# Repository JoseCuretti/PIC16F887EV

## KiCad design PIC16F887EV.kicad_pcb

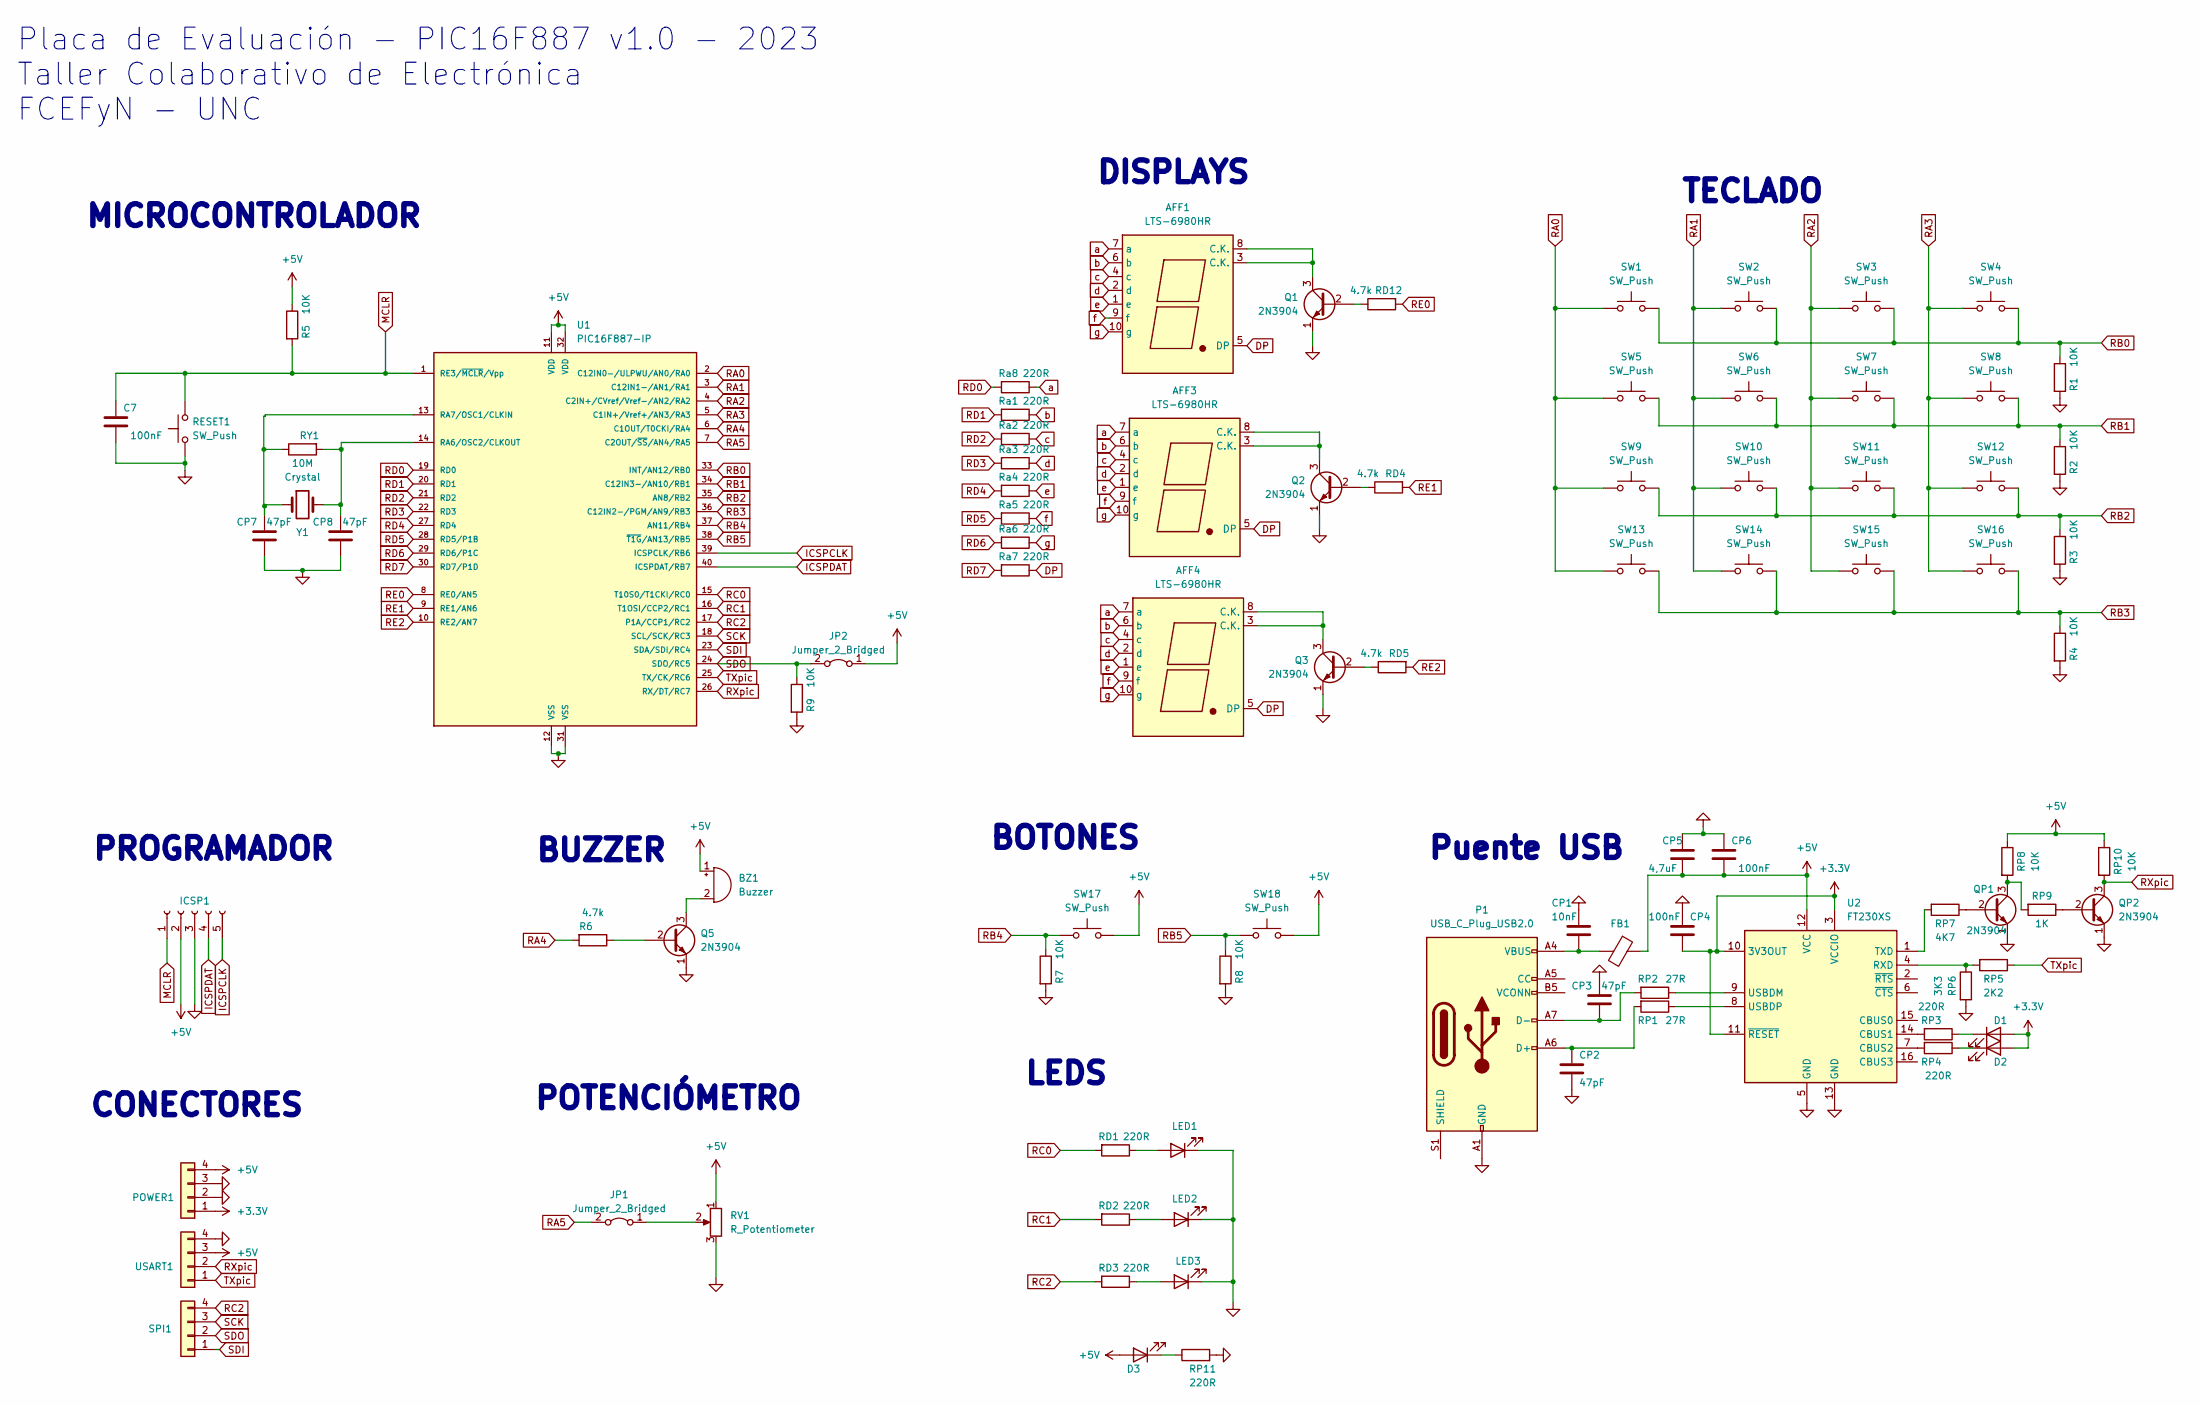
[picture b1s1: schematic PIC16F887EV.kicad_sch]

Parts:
AFF1, AFF3, AFF4: LTS-6980HR; 7SegmentLED_LTS6760_LTS6780
BZ1: Buzzer; MagneticBuzzer_ProSignal_ABT-410-RC
C7: 100nF; C_1206_3216Metric_Pad1.33x1.80mm_HandSolder
CP1: 10nF; C_1206_3216Metric_Pad1.33x1.80mm_HandSolder
CP2, CP3, CP7, CP8: 47pF; C_1206_3216Metric_Pad1.33x1.80mm_HandSolder
CP4, CP6: 100nF; C_1206_3216Metric_Pad1.33x1.80mm_HandSolder
CP5: 4,7uF; C_1206_3216Metric_Pad1.33x1.80mm_HandSolder
D1, D2, D3: LED; LED_1206_3216Metric_Pad1.42x1.75mm_HandSolder
FB1: FerriteBead; L_0805_2012Metric_Pad1.15x1.40mm_HandSolder
ICSP1: Conn_01x05_Socket; PinSocket_1x05_P2.54mm_Vertical
JP1, JP2: Jumper_2_Bridged; PinHeader_1x02_P2.54mm_Vertical
LED1, LED2, LED3: LED; LED_1206_3216Metric_Pad1.42x1.75mm_HandSolder
P1: USB_C_Plug_USB2.0; USB_C_Receptacle_GCT_USB4105-xx-A_16P_TopMnt_Horizontal
POWER1: Conn_01x04; PinSocket_1x04_P2.54mm_Vertical
Q1, Q2, Q3, Q5: 2N3904; SOT-23_Handsoldering
QP1, QP2: 2N3904; SOT-23_Handsoldering
R1, R2, R3, R4, R5, R7, R8, R9: 10K; R_1206_3216Metric_Pad1.30x1.75mm_HandSolder
R6: 4.7k; R_1206_3216Metric_Pad1.30x1.75mm_HandSolder
RD1, RD2, RD3: 220R; R_1206_3216Metric_Pad1.30x1.75mm_HandSolder
RD4, RD5, RD12: 4.7k; R_1206_3216Metric_Pad1.30x1.75mm_HandSolder
RESET1: SW_Push; SW_TS04-66-43-BK-100-SMT
RP1, RP2: 27R; R_1206_3216Metric_Pad1.30x1.75mm_HandSolder
RP3, RP4, RP11: 220R; R_1206_3216Metric_Pad1.30x1.75mm_HandSolder
RP5: 2K2; R_1206_3216Metric_Pad1.30x1.75mm_HandSolder
RP6: 3K3; R_1206_3216Metric_Pad1.30x1.75mm_HandSolder
RP7: 4K7; R_1206_3216Metric_Pad1.30x1.75mm_HandSolder
RP8, RP10: 10K; R_1206_3216Metric_Pad1.30x1.75mm_HandSolder
RP9: 1K; R_1206_3216Metric_Pad1.30x1.75mm_HandSolder
RV1: R_Potentiometer; Potentiometer_Bourns_3299W_Vertical
RY1: 10M; R_1206_3216Metric_Pad1.30x1.75mm_HandSolder
Ra1, Ra2, Ra3, Ra4, Ra5, Ra6, Ra7, Ra8: 220R; R_1206_3216Metric_Pad1.30x1.75mm_HandSolder
SPI1: Conn_01x04; PinSocket_1x04_P2.54mm_Vertical
SW1, SW2, SW3, SW4, SW5, SW6, SW7, SW8, SW9, SW10, SW11, SW12, SW13, SW14, SW15, SW16, SW17, SW18: SW_Push; SW_TS04-66-43-BK-100-SMT
U1: PIC16F887-IP; DIP-40_W15.24mm_LongPads
U2: FT230XS; SSOP-16_3.9x4.9mm_P0.635mm
USART1: Conn_01x04; PinSocket_1x04_P2.54mm_Vertical
Y1: Crystal; Crystal_HC18-U_Vertical

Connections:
+3.3V: CP4.2, D1.2 (A), D2.2 (A), POWER1.1, U2.3 (VCCIO), U2.10 (3V3OUT), U2.11 (~RESET)
+5V: BZ1.1 (-), CP5.2, CP6.2, D3.2 (A), FB1.1, ICSP1.2, JP2.1 (A), POWER1.4, R5.1, RP8.1, RP10.1, RV1.1, SW17.2, SW18.2, U1.11 (VDD), U1.32 (VDD), U2.12 (VCC), USART1.3
DP: AFF1.5 (DP), AFF3.5 (DP), AFF4.5 (DP), Ra7.1
GND: C7.2, CP1.1, CP2.2, CP3.2, CP4.1, CP5.1, CP6.1, CP7.1, CP8.1, ICSP1.3, LED1.1 (K), LED2.1 (K), LED3.1 (K), P1.A1 (GND), P1.A12 (GND), P1.B1 (GND), P1.B12 (GND), POWER1.2, POWER1.3, Q1.1 (E), Q2.1 (E), Q3.1 (E), Q5.1 (E), QP1.1 (E), QP2.1 (E), R1.2, R2.2, R3.2, R4.2, R7.2, R8.2, R9.2, RESET1.1, RP6.2, RP11.2, RV1.3, U1.12 (VSS), U1.31 (VSS), U2.5 (GND), U2.13 (GND), USART1.4
ICSPCLK: ICSP1.5, U1.39 (ICSPCLK/RB6)
ICSPDAT: ICSP1.4, U1.40 (ICSPDAT/RB7)
MCLR: C7.1, ICSP1.1, R5.2, RESET1.2, U1.1 (RE3/~MCLR/Vpp)
unnamed: BZ1.2 (+), Q5.3 (C)
unnamed: CP1.2, FB1.2, P1.A4 (VBUS), P1.A9 (VBUS), P1.B4 (VBUS), P1.B9 (VBUS)
unnamed: D1.1 (K), RP3.1
unnamed: D2.1 (K), RP4.1
unnamed: D3.1 (K), RP11.1
unnamed: JP1.1 (A), RV1.2
unnamed: LED1.2 (A), RD1.1
unnamed: LED2.2 (A), RD2.1
unnamed: LED3.2 (A), RD3.1
unnamed: CP2.1, P1.A6 (D+), RP1.2
unnamed: CP3.1, P1.A7 (D-), RP2.2
unnamed: Q1.2 (B), RD12.1
unnamed: AFF1.3 (C.K.), AFF1.8 (C.K.), Q1.3 (C)
unnamed: Q2.2 (B), RD4.1
unnamed: AFF3.3 (C.K.), AFF3.8 (C.K.), Q2.3 (C)
unnamed: Q3.2 (B), RD5.1
unnamed: AFF4.3 (C.K.), AFF4.8 (C.K.), Q3.3 (C)
unnamed: Q5.2 (B), R6.1
unnamed: QP1.2 (B), RP7.1
unnamed: QP1.3 (C), RP8.2, RP9.2
unnamed: QP2.2 (B), RP9.1
unnamed: CP8.2, RY1.2, U1.14 (RA6/OSC2/CLKOUT), Y1.2
unnamed: CP7.2, RY1.1, U1.13 (RA7/OSC1/CLKIN), Y1.1
unnamed: RP3.2, U2.14 (CBUS1)
unnamed: RP4.2, U2.7 (CBUS2)
unnamed: RP5.2, RP6.1, U2.4 (RXD)
unnamed: RP7.2, U2.1 (TXD)
unnamed: RP2.1, U2.9 (USBDM)
unnamed: RP1.1, U2.8 (USBDP)
RA0: SW1.1, SW5.1, SW9.1, SW13.1, U1.2 (C12IN0-/ULPWU/AN0/RA0)
RA1: SW2.1, SW6.1, SW10.1, SW14.1, U1.3 (C12IN1-/AN1/RA1)
RA2: SW3.1, SW7.1, SW11.1, SW15.1, U1.4 (C2IN+/CVref/Vref-/AN2/RA2)
RA3: SW4.1, SW8.1, SW12.1, SW16.1, U1.5 (C1IN+/Vref+/AN3/RA3)
RA4: R6.2, U1.6 (C1OUT/T0CKI/RA4)
RA5: JP1.2 (B), U1.7 (C2OUT/~SS/AN4/RA5)
RB0: R1.1, SW1.2, SW2.2, SW3.2, SW4.2, U1.33 (INT/AN12/RB0)
RB1: R2.1, SW5.2, SW6.2, SW7.2, SW8.2, U1.34 (C12IN3-/AN10/RB1)
RB2: R3.1, SW9.2, SW10.2, SW11.2, SW12.2, U1.35 (AN8/RB2)
RB3: R4.1, SW13.2, SW14.2, SW15.2, SW16.2, U1.36 (C12IN2-/PGM/AN9/RB3)
RB4: R7.1, SW17.1, U1.37 (AN11/RB4)
RB5: R8.1, SW18.1, U1.38 (~T1G/AN13/RB5)
RC0: RD1.2, U1.15 (T10S0/T1CKI/RC0)
RC1: RD2.2, U1.16 (T1OSI/CCP2/RC1)
RC2: RD3.2, SPI1.4, U1.17 (P1A/CCP1/RC2)
RD0: Ra8.2, U1.19 (RD0)
RD1: Ra1.2, U1.20 (RD1)
RD2: Ra2.2, U1.21 (RD2)
RD3: Ra3.2, U1.22 (RD3)
RD4: Ra4.2, U1.27 (RD4)
RD5: Ra5.2, U1.28 (RD5/P1B)
RD6: Ra6.2, U1.29 (RD6/P1C)
RD7: Ra7.2, U1.30 (RD7/P1D)
RE0: RD12.2, U1.8 (RE0/AN5)
RE1: RD4.2, U1.9 (RE1/AN6)
RE2: RD5.2, U1.10 (RE2/AN7)
RXpic: QP2.3 (C), RP10.2, U1.26 (RX/DT/RC7), USART1.2
SCK: SPI1.3, U1.18 (SCL/SCK/RC3)
SDI: SPI1.1, U1.23 (SDA/SDI/RC4)
SDO: JP2.2 (B), R9.1, SPI1.2, U1.24 (SDO/RC5)
TXpic: RP5.1, U1.25 (TX/CK/RC6), USART1.1
a: AFF1.7 (a), AFF3.7 (a), AFF4.7 (a), Ra8.1
b: AFF1.6 (b), AFF3.6 (b), AFF4.6 (b), Ra1.1
c: AFF1.4 (c), AFF3.4 (c), AFF4.4 (c), Ra2.1
d: AFF1.2 (d), AFF3.2 (d), AFF4.2 (d), Ra3.1
e: AFF1.1 (e), AFF3.1 (e), AFF4.1 (e), Ra4.1
f: AFF1.9 (f), AFF3.9 (f), AFF4.9 (f), Ra5.1
g: AFF1.10 (g), AFF3.10 (g), AFF4.10 (g), Ra6.1

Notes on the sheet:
BUZZER
MICROCONTROLADOR
Placa de Evaluación - PIC16F887 v1.0 - 2023 Taller Colaborativo de Electrónica FCEFyN - UNC
CONECTORES
LEDS
BOTONES
PROGRAMADOR
TECLADO
DISPLAYS
Puente USB
POTENCIÓMETRO

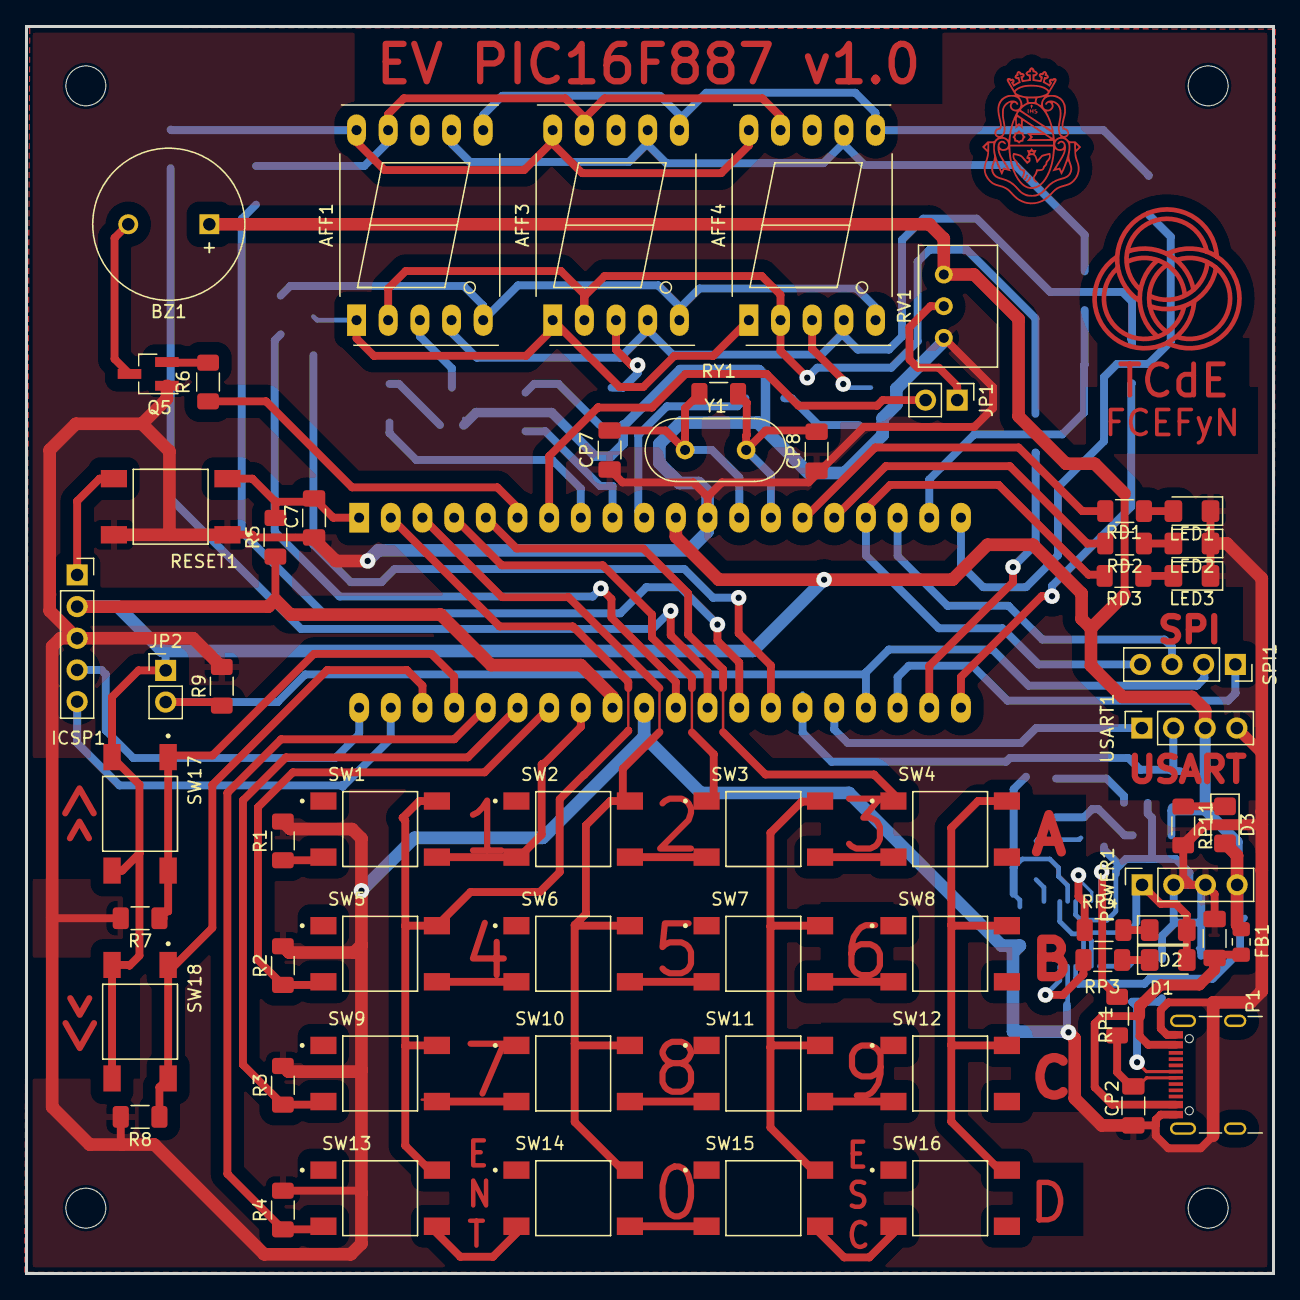
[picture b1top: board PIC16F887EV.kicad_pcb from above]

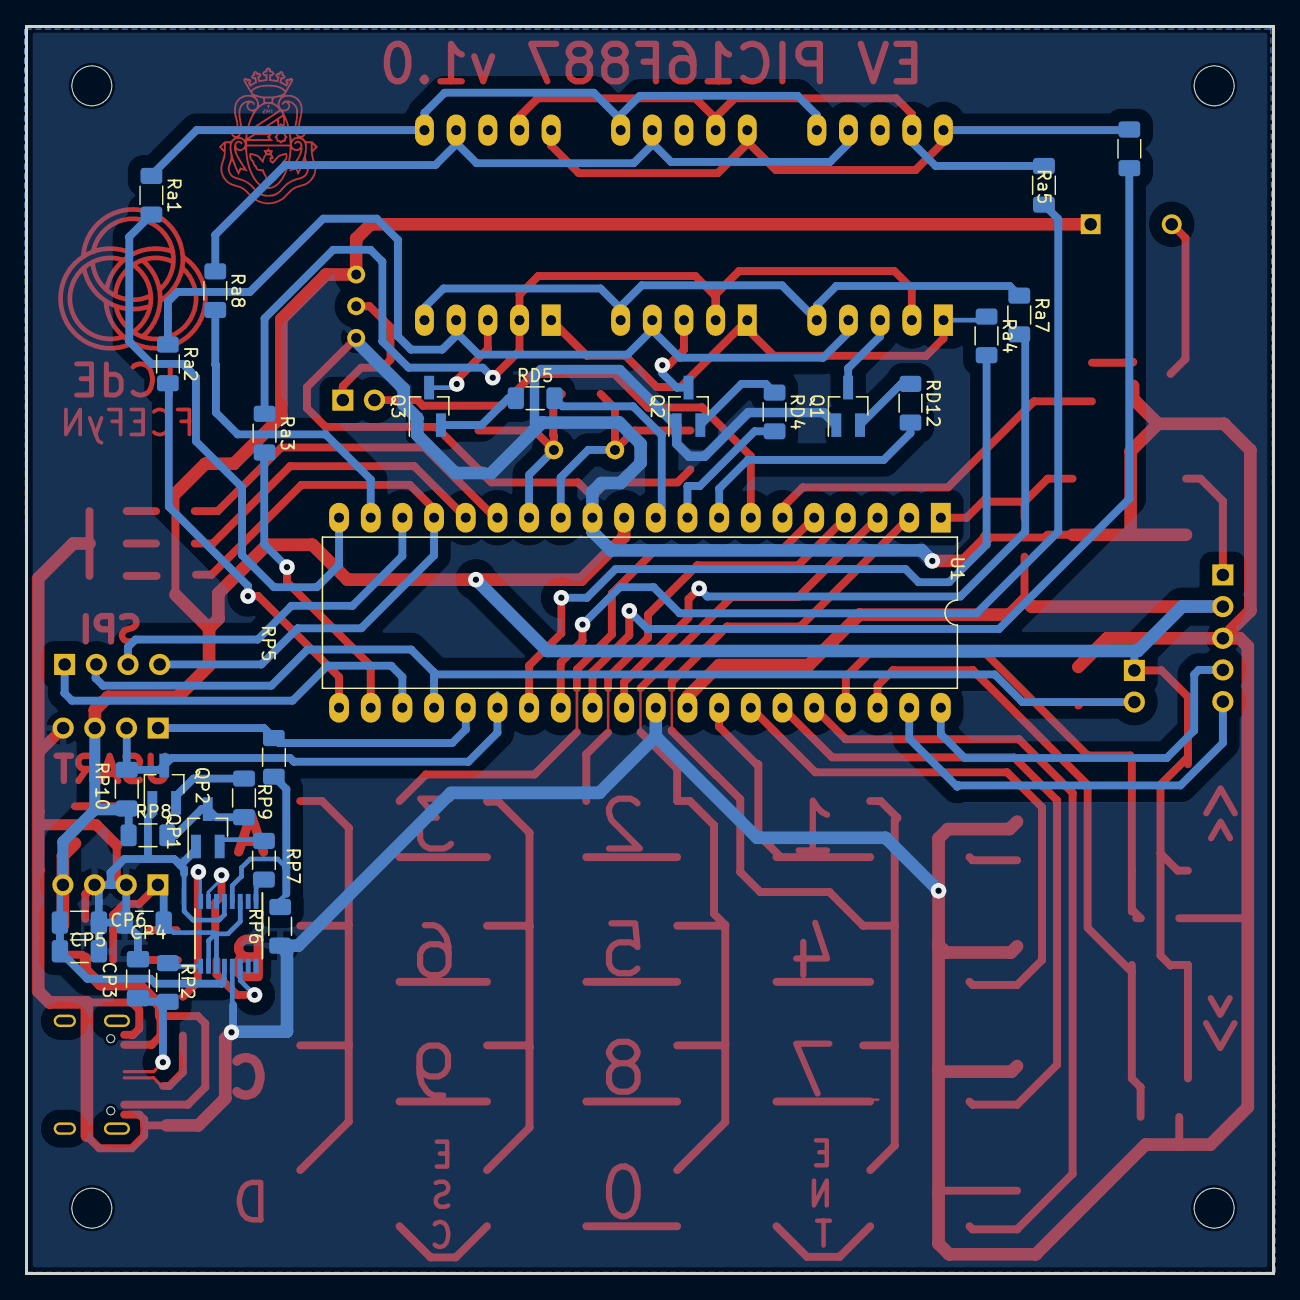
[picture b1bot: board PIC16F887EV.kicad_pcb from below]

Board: 2 copper layers, 100.0 x 100.0 mm, 97 parts (29 on the bottom side), 74 nets.

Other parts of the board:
REF1, REF2, REF3, REF4: MountingHole_3.2mm_M3
TCdE FCEFYN: Logo
TCdE FCEFYN#2: Logo

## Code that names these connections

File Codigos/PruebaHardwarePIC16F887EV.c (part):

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

// CONFIG1
#pragma config FOSC = INTRC_NOCLKOUT// Oscillator Selection bits (INTOSCIO oscillator: I/O function on RA6/OSC2/CLKOUT pin, I/O function on RA7/OSC1/CLKIN)
#pragma config WDTE = OFF       // Watchdog Timer Enable bit (WDT disabled and can be enabled by SWDTEN bit of the WDTCON register)
#pragma config PWRTE = OFF      // Power-up Timer Enable bit (PWRT disabled)
#pragma config MCLRE = ON       // RE3/MCLR pin function select bit (RE3/MCLR pin function is MCLR)
#pragma config CP = OFF         // Code Protection bit (Program memory code protection is disabled)
#pragma config CPD = OFF        // Data Code Protection bit (Data memory code protection is disabled)
#pragma config BOREN = OFF      // Brown Out Reset Selection bits (BOR disabled)
#pragma config IESO = OFF       // Internal External Switchover bit (Internal/External Switchover mode is disabled)
#pragma config FCMEN = OFF      // Fail-Safe Clock Monitor Enabled bit (Fail-Safe Clock Monitor is disabled)
#pragma config LVP = OFF        // Low Voltage Programming Enable bit (RB3 pin has digital I/O, HV on MCLR must be used for programming)

// CONFIG2
#pragma config BOR4V = BOR40V   // Brown-out Reset Selection bit (Brown-out Reset set to 4.0V)
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
#define XTALFREC 4000000     //El oscilador interno anda  a 4 MHz

#define BUZZER  PORTAbits.RA4
#define tABAJO  PORTBbits.RB5
#define tARRIBA PORTBbits.RB4
#define DisplayL PORTEbits.RE2
#define DisplayM PORTEbits.RE1
#define DisplayH PORTEbits.RE0

#define pPROG         PORTCbits.RC5
#define LEDVERDE      PORTCbits.RC0
#define LEDAMARILLO   PORTCbits.RC1
#define LEDROJO       PORTCbits.RC2

static int TECLAS[]={0b00111111,0b00000110,0b01011011,0b01001111,0b01100110,0b01101101,0b01111101,0b00000111,0b01111111,0b01101111,0b01110111,0b01111100,0b00111001,0b01011110} ; // "0" "1" "2" "3" "4" "5" "6" "7" "8" "9" "A" "b" "C" "d"
static int NUMEROS[]={0b00111111,0b00000110,0b01011011,0b01001111,0b01100110,0b01101101,0b01111101,0b00000111,0b01111111,0b01101111} ; // "0" "1" "2" "3" "4" "5" "6" "7" "8" "9"
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
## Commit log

2023-09-24 Add files via upload
    Commit inicial
2023-09-29 Add files via upload
    con corto prueba
2023-10-06 Buzzer Agregado
    Hay que elegir el footprint correcto
2023-10-06 Add files via upload
    Esquemático basado en proyecto de Digital 2
2023-10-06 cambio de pin a n 7
2023-10-06 DoblePin
2023-10-06 cambio a pin 23
2023-10-12 USB-C y FT230X
    Agregado Puente USB y conector USB-C
2023-10-12 Keypad
    Teclado 4x4 sin pull ups externas
2023-10-12 display SA56-11SRWA
2023-10-14 Delete PIC16F887EV-backups directory
    Usando versionado, no debería hacer falta tener los back-up en repositorio...
2023-10-14 SW1 Huella
    Cambio Botón SW1, ahora con huella
2023-10-16 Puente USB completo
    Agregué y conecté todos los componentes del Puente USB-USART en el esquemático
2023-10-16 Ignore carpeta backups
2023-10-19 Actualización teclado
2023-10-19 Avance parcial
    Leds + Potenciómetro + ICSP
2023-10-19 Reset
2023-10-19 Actualizacion
2023-10-19 Leds smd 1206
2023-10-19 Corrección leds
2023-10-19 Socket ICSP
2023-10-19 Buzzer
2023-10-19 Displays
2023-10-19 Actualización
2023-10-19 auto save
2023-10-20 Actualizacion Puente + Huellas
    Agregue componentes de interfaz entre PIC (5V) y puente USB (3V3).
    Cambie las huellas de transistores a SMD.
    Cambie el BJT 2N2222 por un 3904
2023-10-21 LimitesPCB+Reglas
    Agregado el cuadrado de 10cmx10cm y algunas reglas de enrutamiento
2023-10-22 Avance esquemático
    Cristal externo + Teclado en puertos A y B con pulldown + huella potenciometro + pin de programación
2023-10-24 Distribución de componentes dentro del rectángulo de 10x10cm
    Moví los componentes y los agrupé aproximadamente donde podrían ir dejando el PIC y el puente USB del lado inferior.
    A los switchs de teclado les cambié la huella por una con modelo 3d pero del mismo footprint
2023-10-24 Tornillos + Huella Potenciometro
    Agregado de 4 huecos para tornillos de montaje
    Cambio de huella del potenciómetro
2023-10-25 Ruteo provisorio capa frontal
2023-10-25 Logo
    Logo Taller Colaborativo de Electronica + Nombre de placa
2023-10-25 Jumpers modificados
    tuve que cambiar la ubicación de uno porque estaba sobre el PIC
2023-10-25 unc logo
    agregue un mini logo de unc
2023-10-26 Texto y espaciado de teclado - jumper desplazado
    * Agregue texto en el formato de 4x4, espesor 0.5 . --> Puede cambiarse, opte por ese formado por el teclado matricial comercial.
    * Moví el jumper ,ya que se encontraba muy cerca del teclado y podría ser incomodo presionar.
    * Conexiones comunes como +5v o GND en el PIC las desconecte para tener mas rutas en el ruteo (estas están conectadas internamente en el PIC)
    * Conexión entre patas comunes en los pulsadores también las borre, sé que son comunes de a par, podría no tener sentido unirlas, ya que internamente lo están. (igual
    es opcional, se puede volver a agregar)
    * Opte por poner en un lateral las letras del teclado ya que
2023-10-26 Bloque displays con vías
2023-10-26 Teclado
    Fer hace un rato pifíe con el teclado! acabo de volverlo a rutear más o menos como lo habías ruteado vos, chequealo y cambialo cualquier cosa!
2023-10-26 Buzzer y Jumper para Pickit
    Ruteo del buzzer y ajuste de espacio para ver si entran los displays en la parte de arriba.
    A los 3 displays los dejé mas o menos acomodados a un costado para después ponerlos en la placa y conectar al pic por la capa trasera.
2023-10-27 Ubicación de Displays
    Me están quedando pendientes las 8 Res de cada segmento
2023-10-27 Conectores + Etiquetas Teclas
    Agregado de conectores de USART SPI y POWER
    Rescate de los números y letras de las teclas, con modificación del * y #
2023-10-27 Puente USB ruteado
2023-10-30 agrego + tamaños de logos unc
2023-10-31 USB completo
    Termine la parte de USB y conectores
2023-11-01 agrego mas tamaños de logos
2023-11-01 Logo tamaño 2
2023-11-03 Ruteo de GND y resistencias de los displays.
2023-11-03 Agregado de Texto a teclados y simbolo a Pulsador
    Al texto y símbolos los agrupe, para ambos caso sobre la capa F.Cu le puse una F.Mask. Asi el cobre esta al frente.
2023-11-03 Agregado de F.Mask a logos
    se quito el rectángulo de F.Mask de los logos y se superpuso el mismo logo con otra capa, así queda descubierto el cobre sobre el mismo.
2023-11-05 Displays ruteados
    Falta la conexión de las pistas de 5V que están en distintas capas
2023-11-05 Version Final 1.0
    Algunos footprint cambiados, repaso de ancho de pistas y tamaño de vias, agregado de plano de masa
2023-11-11 Modelo 3D para los nuenos switches
    asigné el modelo del switch al footprint del primer botón del teclado. El diseño está en la carpeta del proyecto como un .step no pude asignar el modelo a todos los botones al mismo tiempo, si alguie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
2023-11-16 Modelo 3D para los interruptores
    Ya tienen su modelo los interruptores, no logré hacerlo con el script y lo hice un poco a mano modificando el archivo del PCB desde el bloc de notas.
    Fue al menos más rápido que asignando una por una desde el KiCAD
2024-01-21 bootloader y mas
2024-01-22 Programa Prueba Hardware
    .c y .hex de programa que prueba LEDS, DISPLAYS, BUZZER, Teclas y USART
2024-02-06 Acomodo SCH
    Acomodo un poco los modulos del esquematico
2024-02-06 Valores PCB acomodados
    Acomodo los nombres y valores de los componentes
2024-02-20 agrego PICkit3- Software
